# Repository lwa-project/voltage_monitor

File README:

Line (Voltage) Monitoring Software
==================================

This directory contains a collection of software for interfacing with a
TekPower TP4000ZC digital multi-meter (DMM) for monitoring AC line voltage.

This software depends on the following python modules:
  * tp4000zc.py (from https://github.com/Xuth/tp4000_dmm)
  * pySerial
  * pytz
  * wxPython

Contents
--------
tp4000zc.py
  Python module for interfacing with the DMM and reading data.

lineMonitor.py
  Python script for logging line voltages.

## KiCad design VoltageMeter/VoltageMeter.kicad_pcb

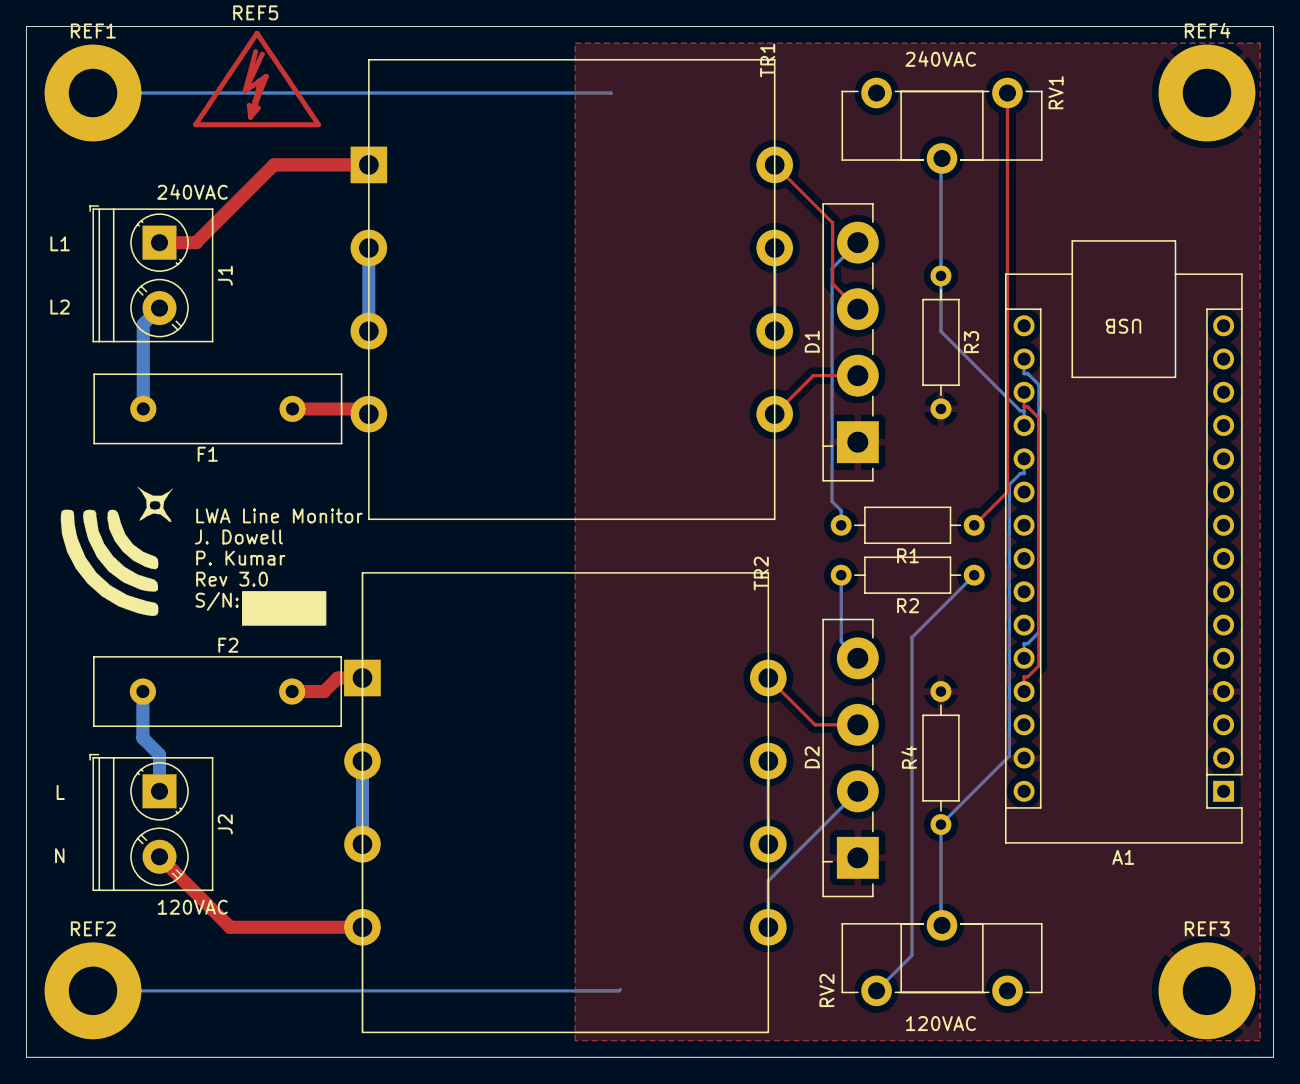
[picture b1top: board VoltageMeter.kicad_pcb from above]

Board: 2 copper layers, 95.2 x 78.7 mm, 20 parts (0 on the bottom side), 23 nets.

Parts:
A1: Arduino_Nano_v3.x; Arduino_Nano
D1, D2: B40C5000-3x00A; Diode_Bridge_Vishay_GBL
F1, F2: Fuse; Fuse_Littelfuse-LVR100
J1, J2: Conn_01x02_Male; TerminalBlock_Phoenix_PT-1,5-2-5.0-H_1x02_P5.00mm_Horizontal
R1, R2: 665k; R_Axial_DIN0207_L6.3mm_D2.5mm_P10.16mm_Horizontal
R3, R4: 120k; R_Axial_DIN0207_L6.3mm_D2.5mm_P10.16mm_Horizontal
REF1, REF2, REF3, REF4: MountingHole_3.7mm_Pad
REF5: Symbol_HighVoltage_Type2_CopperTop_VerySmall
RV1, RV2: 10k; Potentiometer_Piher_PT-15-H05_Horizontal
TR1, TR2: TRANSF6; 4900-XXXXRA60

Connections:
120VAC_ADC: A1.20, R4.1, RV2.2
120VAC_L: F2.1, J2.1
120VAC_N: J2.2, TR2.4
240VAC_ADC: A1.19, R3.1, RV1.2
240VAC_L1: J1.1, TR1.1
240VAC_L2: F1.2, J1.2
+3VDC3: A1.17, A1.26
+5VDC: A1.18, A1.27
GND: A1.4, A1.29, D1.1, D2.1, R3.2, R4.2, REF1.1, REF2.1, REF3.1, REF4.1
unnamed: D1.2, TR1.8
unnamed: D1.3, TR1.5
unnamed: D1.4, R1.2
unnamed: D2.2, TR2.8
unnamed: D2.3, TR2.5
unnamed: D2.4, R2.2
unnamed: F1.1, TR1.4
unnamed: F2.2, TR2.1
unnamed: R1.1, RV1.1
unnamed: R2.1, RV2.1
unnamed: TR1.2, TR1.3
unnamed: TR1.6, TR1.7
unnamed: TR2.2, TR2.3
unnamed: TR2.6, TR2.7

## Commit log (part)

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2017-09-22 Initial commit of the line voltage monitoring software for the stations.
2017-09-25 Added a variety of features to get lineMonitor.py to a new production state. Added in supplemental scripts to help watch lineMonitor.py and send out e-mail alerts.
2017-10-18 Added a CLI tool for checking on the voltages. Also, working on cleaning up how flickers are detected and notified.
2017-10-18 Fixed a couple of problem in the LineMonitoring tools now that we are trying to deploy at LWA1.
2017-10-27 Fixed a bug in lineMonitor.py that caused the code not to notify brief power flickers.
2017-10-27 Added reporting of FLICKER, OUTAGE, and CLEAR messages to lineMonitorCLI.py.
2017-10-30 Tweaked the duplicate message suppression code so that at least something shows up in the runtime logs for lineMonitor.py.
2017-10-30 A few small tweaks to how lineMonitor.py and sendPowerEmail.py run. This splits the stdout/stderr output locations between the two so that it is easier to keep up with what is happening. Also, added 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
2017-11-19 Fixed a typo in lineMonitor.py.
2017-12-15 Update the alert e-mail address for sendPowerEmail.py.
2018-10-23 Worked on moving the LineMonitoring software over to spaces instead of tabs. Fixed an e-mail address problem in sendPowerEmail.py. Fixed a problem sending out flicker e-mails in sendPowerEmail.py. Ad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
2018-10-23 Fixed a missed tab in sendPowerEmail.py.
2019-03-06 Applied static analysis to the LineMonitoring software and fixed a few problems.
2019-03-08 Added a rate limiter to the flicker e-mail messages.
2019-03-13 Changed how the line monitor works with regards to flickers. Flickers are now intended to be self-clearing events that expire. Clears are only sent after power has been restored after an outage.
2019-03-13 Changed the location of the state directory for the sendPowerEmail.py script.
2019-03-13 Added disk-based outage state to the lineMonitory.py script so that long outages that take down the comptuer can be properly cleared. Changed the default ports for the DMMs.
2019-03-14 Major change to the line monitoring software to only send clear after the power has been stable for a pre-determined amount of time (currently 5 minutes). This should help consolidate all of the powe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
2019-03-14 Fixed a typo: start120 -> state120.
2019-03-14 Added .lm-state to svn:ignore.
2019-04-04 Fixed a bug in MultipartPostHandler.py I introduced a few weeks ago.
2019-05-07 Small change to how the internal state is updated in lineMonitor.py to keep flickers from preventing 'outage cleared' from being sent.
2019-05-10 Reworked the state inside lineMonitor.py to make it more robust. Added 'defaults.cfg' files for both stations to make dealing with the configuration easier. Added logging for when a power outage is r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
2019-05-10 Fixed a bug in sendPowerEmail.py that caused the script to crash if an invalid message was received.
2019-05-31 Cleaned up the config. file parsing in lineMonitor.py. Fixed a problem clearing flickers and outages.
2019-05-31 Cleaned up the init scripts and added a time mark to the sendPowerEmail.py stdout/err log files.
2019-08-16 Updated the lineMonitor.py script to work with the new LWA voltage monitoring boards. This inludes a new lvmb.py module to interface with the board that replaces the tp4000zc.py module.
2019-08-16 Fixed a typo in where the 120V logs are saved and added a new -f/--foreground option to disable daemonization.
2019-08-16 Cleaned up the exception handling a little.
2019-08-16 More cleaning up of the exception handling.
2019-08-16 More cleanup inside lvmb.py.
2019-08-16 Updated the LineMonitoring documentation with the schematics for the LWA voltage monitoring board.
2019-08-27 Updated the defaults.cfg.* files to use an actual 10% margin on the 240V line.
2019-09-03 Added the Arduino firmware for the line monitor.
2019-09-09 Moved the line monitoring software over to argparse.
2019-09-09 Applied print_function to the line monitoring software.
2019-09-10 Added logging for problems writing to the state file.
2019-09-10 Cleaned up the exception handling a little more.
2019-09-10 Moved the line monitoring software from thread to threading.
2019-09-10 Fixed an import problem thread->threading.
2019-09-10 Replaced file with open in the lightning detector and line monitor software.
2019-09-11 Switched over to the requests module for file uploads.
2019-09-11 Removed the MultipartPostHandler.py module from several places where we have switched over to requests.
2019-09-11 More work on the line monitoring and lightning detector scripts to get them ready for Python3.
2019-09-11 More work on the line monitoring scripts for Python3.
2019-09-11 Even more work on getting the line monitoring and lightning detector software working on Python3.
2020-03-24 Renamed some of the scripts to make them more consistent with the repository name.
2020-03-24 Added a .gitignore file.
2020-03-24 Removed the old subversion stuff and updated the .gitignore file.
2020-04-22 Added back in more detailed versioning info.
2021-06-30 Move to the new mailing list.
2021-07-19 Wait five minutes before sending an 'all-clear' after a power outage.
2021-07-19 Updated for Arduino.
2021-07-19 Rename
2021-07-19 Formatting.
2021-12-09 Use udev to get all stations running on the same defaults.cfg file.
2022-03-21 Use the ScienceDMZ for uploads to the archive.
2022-03-30 Ignore the name mismatch on the SSL cert.
2022-03-31 Typo.
2022-06-08 Gmail update.
2022-06-08 Add LWA-NA.
2022-09-09 Move over to a JSON-based configuration file.
2022-09-09 Indentation fix.
2022-09-09 Switch to Py3.
2022-09-09 Missing comma.
2022-09-09 It's a string.
2022-09-09 logging_dir -> log_directory
2022-09-09 It's .json now.
2022-09-09 Switch to systemd service files.
2022-09-09 Copy and paste stikes again.
2022-09-09 Don't daemonize with systemd.
2022-09-09 Added a requirements.txt that will get the services running.
2022-09-15 Fight list.unm.edu.
2022-09-15 Update the reply-to field.
2023-01-06 Switch over to lwa_auth for POST requests.
2023-01-07 Switch over to lwa_auth for secrets managment.
2023-01-07 Email fixes.
2023-01-07 GPL v2.
2023-08-16 Back to alliance.
2024-12-11 Add a small amount of grace time (60 s) to when the a power outage is cleared after a restart.
2024-12-11 Slightly longer grace time of 120 s.
2024-12-11 I think it's less about the grace time and more about having a better reference point to figure out when problems have cleared.
2025-01-21 We need the Arduino device for the voltage monitor to work.
2025-01-30 Combine the 120V and 240V into a single state file. Plus, switch to JSON for the state file.
2025-02-01 Give this version a shot.
2025-02-04 Add a test suite for voltageMonitor.py to check that it detects/recovers from events correctly.
2025-02-04 Fix the timestamp going into the state file. Plus, work on making this work with a unit test.
2025-02-04 Test sendPowerEmail.py.
2025-02-04 Setup testing.
2025-02-04 Missing dependency.
2025-02-04 Skip lwa_auth for now.
2025-02-04 Minimal extra software.
2025-02-04 Dummy lwa_auth.
2025-11-06 Add in PCB info.
2025-11-06 A few updates to clean things up.
2025-11-06 Ignore some KiCAD files.
2026-03-11 Move over to timezone-aware datetimes.
2026-03-26 Run as ops, not root.
2026-03-26 Tabs to spaces.
